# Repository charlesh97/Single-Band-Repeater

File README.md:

# Single Band Repeater
## Uplink 698-719MHz
## Downlink 728-746MHz

Archived project. [Schematic](https://gitlab.com/chood2/single-band-repeater/-/blob/main/singleBandRepeater.pdf),[PCB](https://gitlab.com/chood2/single-band-repeater/-/blob/main/Screen%20Shot%202020-11-10%20at%2012.03.37%20PM.png)

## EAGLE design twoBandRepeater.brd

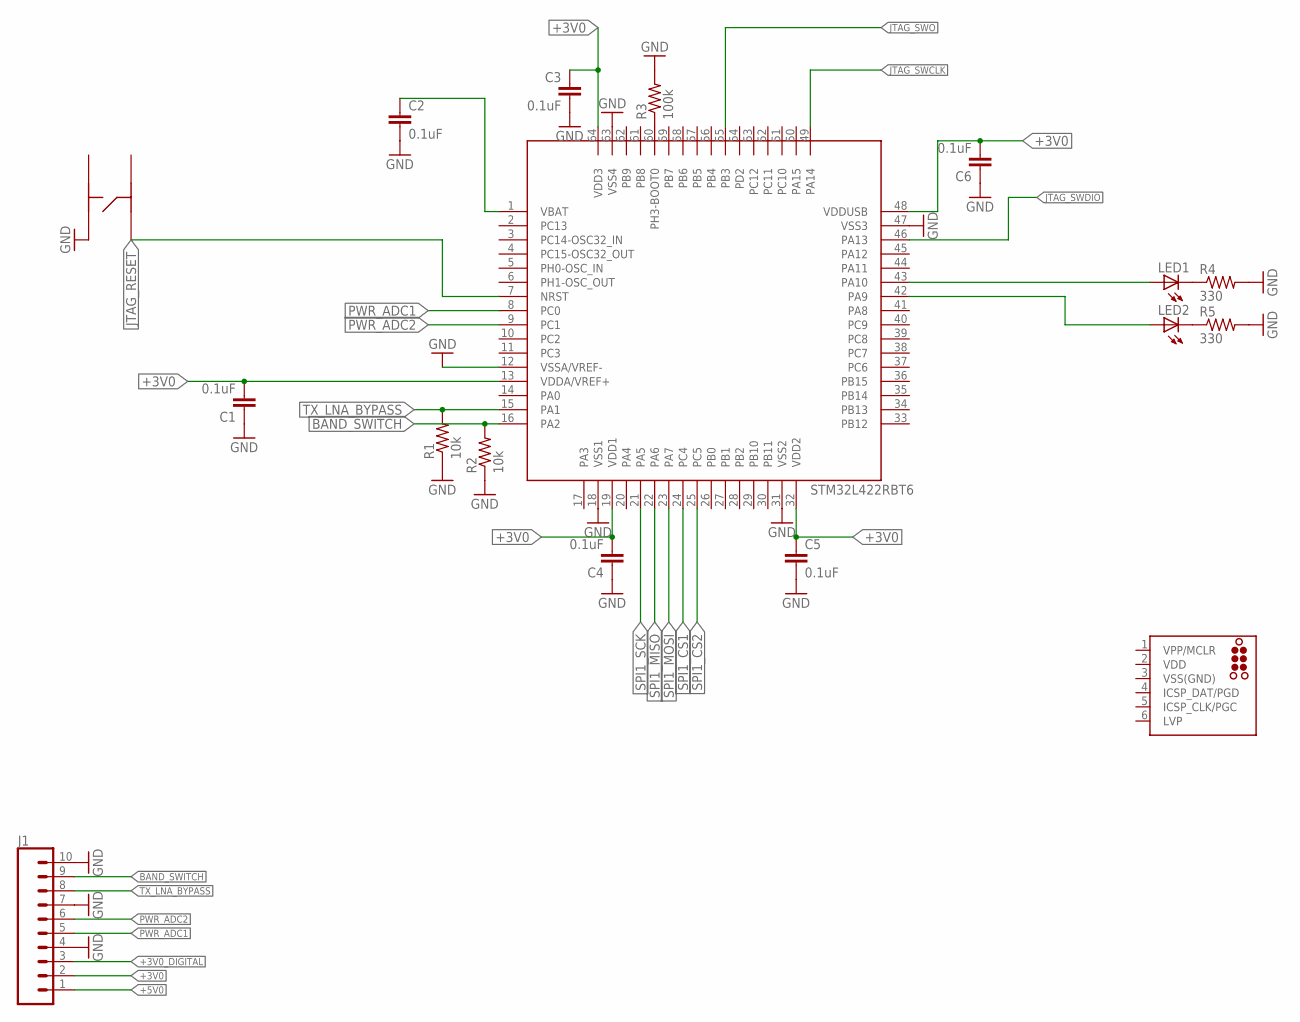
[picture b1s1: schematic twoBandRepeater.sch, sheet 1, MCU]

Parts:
C1, C2, C3, C4, C5, C6: 0.1uF; C0402
J1: CONN_10"; 1X10
J2: TC2030-MCP
LED1, LED2: LEDCHIP-LED0603; CHIP-LED0603
R1, R2: 10k; R0402
R3: 100k; R0402
R4, R5: 330; R0402
S1: KMR731NG
U1: STM32L422RBT6; QFP50P1200X1200X160-64

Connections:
+3V0: C1.2, C3.1, C4.2, C5.1, C6.2, J1.2, U1.13 (VDDA/VREF+), U1.19 (VDD1), U1.32 (VDD2), U1.48 (VDDUSB), U1.64 (VDD3); also elsewhere on the board
+3V0_DIGITAL: J1.3; also elsewhere on the board
+5V0: J1.1; also elsewhere on the board
BAND_SWITCH: J1.9, R2.2, U1.16 (PA2); also elsewhere on the board
GND: C1.1, C2.2, C3.2, C4.1, C5.2, C6.1, J1.4, J1.7, J1.10, R1.1, R2.1, R3.2, R4.2, R5.2, S1.P$3, U1.12 (VSSA/VREF-), U1.18 (VSS1), U1.31 (VSS2), U1.47 (VSS3), U1.63 (VSS4); also elsewhere on the board
JTAG_RESET: S1.P$2, U1.7 (NRST)
JTAG_SWCLK: U1.49 (PA14)
JTAG_SWDIO: U1.46 (PA13)
JTAG_SWO: U1.55 (PB3)
unnamed: C2.1, U1.1 (VBAT)
unnamed: LED1.C, R4.1
unnamed: LED2.C, R5.1
unnamed: LED2.A, U1.42 (PA9)
unnamed: LED1.A, U1.43 (PA10)
unnamed: R3.1, U1.60 (PH3-BOOT0)
PWR_ADC1: J1.5, U1.8 (PC0); also elsewhere on the board
PWR_ADC2: J1.6, U1.9 (PC1); also elsewhere on the board
SPI1_CS1: U1.24 (PC4); also elsewhere on the board
SPI1_CS2: U1.25 (PC5); also elsewhere on the board
SPI1_MISO: U1.22 (PA6); also elsewhere on the board
SPI1_MOSI: U1.23 (PA7); also elsewhere on the board
SPI1_SCK: U1.21 (PA5); also elsewhere on the board
TX_LNA_BYPASS: J1.8, R1.2, U1.15 (PA1); also elsewhere on the board
VDD: J2.2 (VDD)
VSS(GND): J2.3 (VSS(GND))

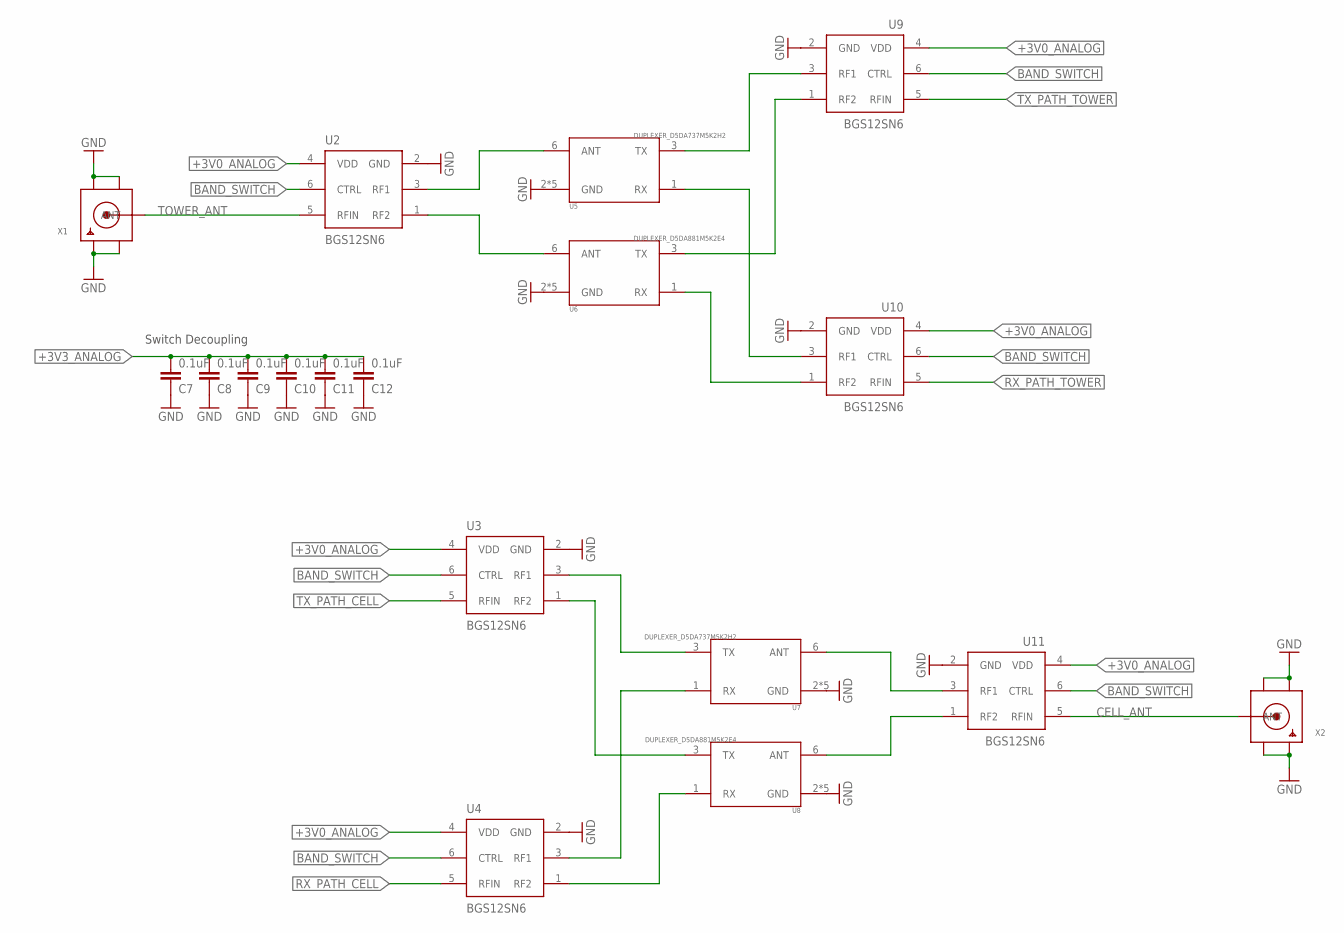
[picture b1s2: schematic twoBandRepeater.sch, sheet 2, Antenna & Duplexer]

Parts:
C7, C8, C9, C10, C11, C12: 0.1uF; C0402
U2, U3, U4, U9, U10, U11: BGS12SN6; INF-PG-TSNP-6-2
U5, U7: DUPLEXER_D5DA737M5K2H2; TAIYO_YUDEN_DUPLEX_1.8X1.4
U6, U8: DUPLEXER_D5DA881M5K2E4; TAIYO_YUDEN_DUPLEX_1.8X1.4
X1, X2: SMACONNECTORSMA_DIP; SMA_DIP

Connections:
+3V0_ANALOG: U2.4 (VDD), U3.4 (VDD), U4.4 (VDD), U9.4 (VDD), U10.4 (VDD), U11.4 (VDD); also elsewhere on the board
+3V3_ANALOG: C7.2, C8.2, C9.2, C10.2, C11.2, C12.2
BAND_SWITCH: U2.6 (CTRL), U3.6 (CTRL), U4.6 (CTRL), U9.6 (CTRL), U10.6 (CTRL), U11.6 (CTRL); also elsewhere on the board
CELL_ANT: U11.5 (RFIN), X2.ANTENNA (ANT)
GND: C7.1, C8.1, C9.1, C10.1, C11.1, C12.1, U2.2 (GND), U3.2 (GND), U4.2 (GND), U5.2 (GND), U5.4 (GND), U5.5 (GND), U5.7 (GND), U5.8 (GND), U6.2 (GND), U6.4 (GND), U6.5 (GND), U6.7 (GND), U6.8 (GND), U7.2 (GND), U7.4 (GND), U7.5 (GND), U7.7 (GND), U7.8 (GND), U8.2 (GND), U8.4 (GND), U8.5 (GND), U8.7 (GND), U8.8 (GND), U9.2 (GND), U10.2 (GND), U11.2 (GND), X1.GND1, X1.GND2, X1.GND3, X1.GND4, X2.GND1, X2.GND2, X2.GND3, X2.GND4; also elsewhere on the board
unnamed: U2.3 (RF1), U5.6 (ANT)
unnamed: U2.1 (RF2), U6.6 (ANT)
unnamed: U5.3 (TX), U9.3 (RF1)
unnamed: U6.3 (TX), U9.1 (RF2)
unnamed: U5.1 (RX), U10.3 (RF1)
unnamed: U6.1 (RX), U10.1 (RF2)
unnamed: U7.6 (ANT), U11.3 (RF1)
unnamed: U8.6 (ANT), U11.1 (RF2)
unnamed: U3.3 (RF1), U7.3 (TX)
unnamed: U3.1 (RF2), U8.3 (TX)
unnamed: U4.3 (RF1), U7.1 (RX)
unnamed: U4.1 (RF2), U8.1 (RX)
RX_PATH_CELL: U4.5 (RFIN); also elsewhere on the board
RX_PATH_TOWER: U10.5 (RFIN); also elsewhere on the board
TOWER_ANT: U2.5 (RFIN), X1.ANTENNA (ANT)
TX_PATH_CELL: U3.5 (RFIN); also elsewhere on the board
TX_PATH_TOWER: U9.5 (RFIN); also elsewhere on the board

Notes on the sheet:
Switch Decoupling

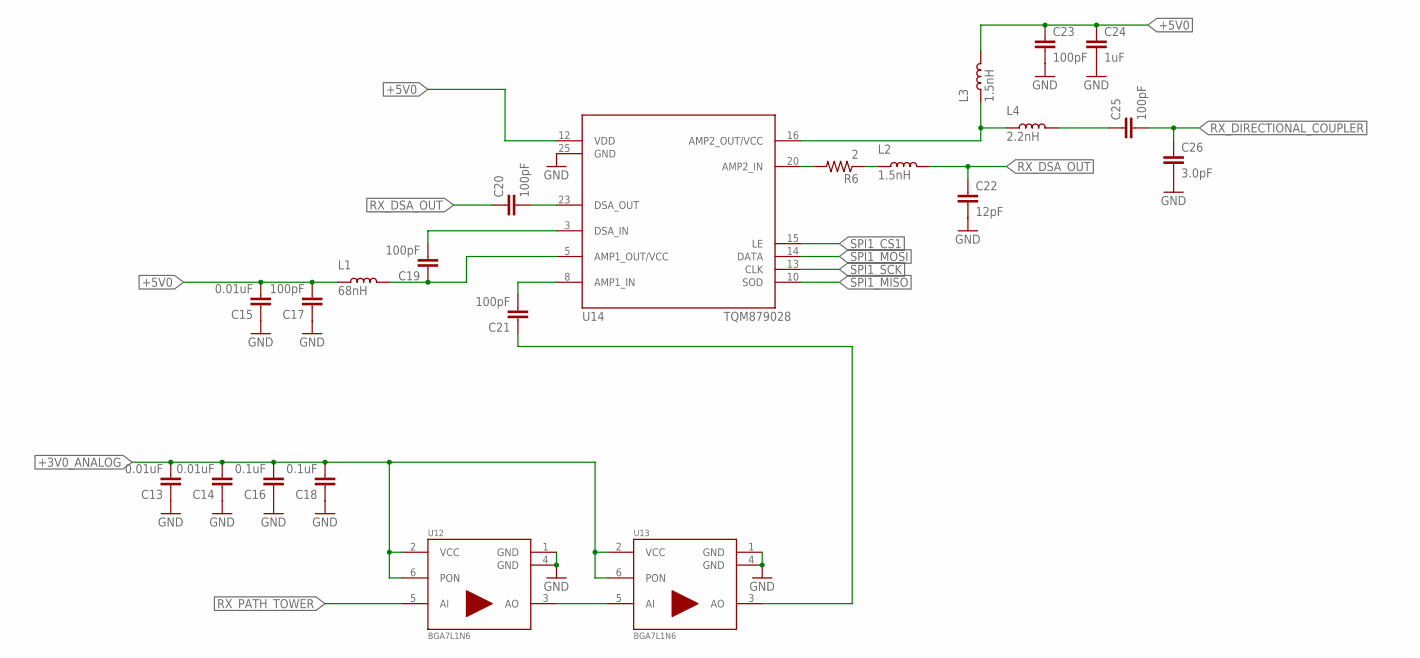
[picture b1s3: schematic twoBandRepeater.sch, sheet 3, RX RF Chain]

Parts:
C13, C14, C15: 0.01uF; C0402
C16, C18: 0.1uF; C0402
C17, C19, C20, C21, C23, C25: 100pF; C0402
C22: 12pF; C0402
C24: 1uF; C0402
C26: 3.0pF; C0402
L1: 68nH; 0402
L2, L3: 1.5nH; 0402
L4: 2.2nH; 0402
R6: 2; R0402
U12, U13: BGA7L1N6; INF-PG-TSNP-6-2
U14: TQM879028; QFN50P400X400X100-25T270N

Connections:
+3V0_ANALOG: C13.2, C14.2, C16.2, C18.2, U12.2 (VCC), U12.6 (PON), U13.2 (VCC), U13.6 (PON); also elsewhere on the board
+5V0: C15.2, C17.2, C23.1, C24.1, L1.1, L3.2, U14.12 (VDD); also elsewhere on the board
GND: C13.1, C14.1, C15.1, C16.1, C17.1, C18.1, C22.2, C23.2, C24.2, C26.2, U12.1 (GND), U12.4 (GND), U13.1 (GND), U13.4 (GND), U14.25 (GND); also elsewhere on the board
unnamed: U12.3 (AO), U13.5 (AI)
unnamed: C21.1, U13.3 (AO)
unnamed: C21.2, U14.8 (AMP1_IN)
unnamed: C19.1, L1.2, U14.5 (AMP1_OUT/VCC)
unnamed: C20.2, U14.23 (DSA_OUT)
unnamed: C19.2, U14.3 (DSA_IN)
unnamed: L3.1, L4.1, U14.16 (AMP2_OUT/VCC)
unnamed: L2.1, R6.1
unnamed: R6.2, U14.20 (AMP2_IN)
unnamed: C25.1, L4.2
RX_DIRECTIONAL_COUPLER: C25.2, C26.1; also elsewhere on the board
RX_DSA_OUT: C20.1, C22.1, L2.2
RX_PATH_TOWER: U12.5 (AI); also elsewhere on the board
SPI1_CS1: U14.15 (LE); also elsewhere on the board
SPI1_MISO: U14.10 (SOD); also elsewhere on the board
SPI1_MOSI: U14.14 (DATA); also elsewhere on the board
SPI1_SCK: U14.13 (CLK); also elsewhere on the board

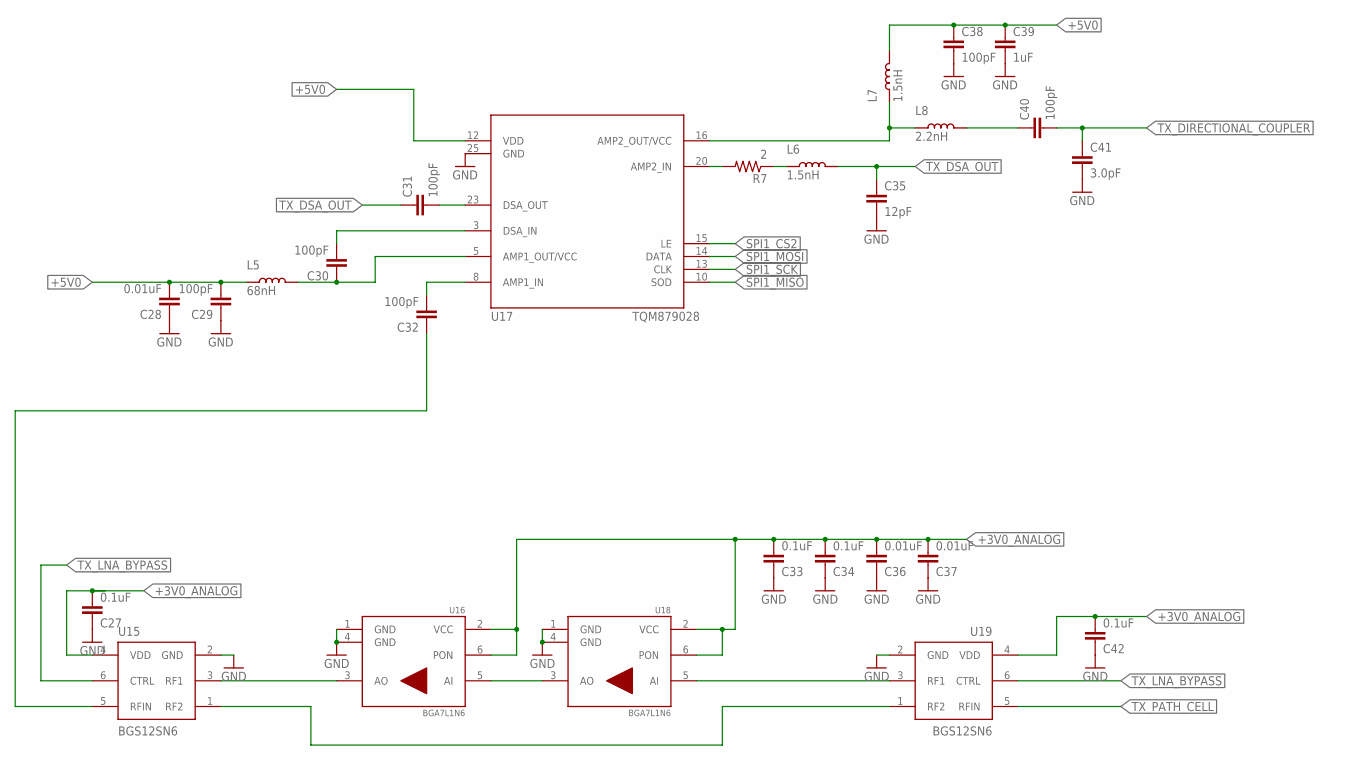
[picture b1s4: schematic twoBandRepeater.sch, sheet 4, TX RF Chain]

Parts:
C27, C33, C34, C42: 0.1uF; C0402
C28, C36, C37: 0.01uF; C0402
C29, C30, C31, C32, C38, C40: 100pF; C0402
C35: 12pF; C0402
C39: 1uF; C0402
C41: 3.0pF; C0402
L5: 68nH; 0402
L6, L7: 1.5nH; 0402
L8: 2.2nH; 0402
R7: 2; R0402
U15, U19: BGS12SN6; INF-PG-TSNP-6-2
U16, U18: BGA7L1N6; INF-PG-TSNP-6-2
U17: TQM879028; QFN50P400X400X100-25T270N

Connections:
+3V0_ANALOG: C27.2, C33.2, C34.2, C36.2, C37.2, C42.2, U15.4 (VDD), U16.2 (VCC), U16.6 (PON), U18.2 (VCC), U18.6 (PON), U19.4 (VDD); also elsewhere on the board
+5V0: C28.2, C29.2, C38.1, C39.1, L5.1, L7.2, U17.12 (VDD); also elsewhere on the board
GND: C27.1, C28.1, C29.1, C33.1, C34.1, C35.2, C36.1, C37.1, C38.2, C39.2, C41.2, C42.1, U15.2 (GND), U16.1 (GND), U16.4 (GND), U17.25 (GND), U18.1 (GND), U18.4 (GND), U19.2 (GND); also elsewhere on the board
unnamed: U16.5 (AI), U18.3 (AO)
unnamed: C32.2, U17.8 (AMP1_IN)
unnamed: C30.1, L5.2, U17.5 (AMP1_OUT/VCC)
unnamed: C30.2, U17.3 (DSA_IN)
unnamed: C31.2, U17.23 (DSA_OUT)
unnamed: L6.1, R7.1
unnamed: R7.2, U17.20 (AMP2_IN)
unnamed: L7.1, L8.1, U17.16 (AMP2_OUT/VCC)
unnamed: C40.1, L8.2
unnamed: U15.3 (RF1), U16.3 (AO)
unnamed: U18.5 (AI), U19.3 (RF1)
unnamed: U15.1 (RF2), U19.1 (RF2)
unnamed: C32.1, U15.5 (RFIN)
SPI1_CS2: U17.15 (LE); also elsewhere on the board
SPI1_MISO: U17.10 (SOD); also elsewhere on the board
SPI1_MOSI: U17.14 (DATA); also elsewhere on the board
SPI1_SCK: U17.13 (CLK); also elsewhere on the board
TX_DIRECTIONAL_COUPLER: C40.2, C41.1; also elsewhere on the board
TX_DSA_OUT: C31.1, C35.1, L6.2
TX_LNA_BYPASS: U15.6 (CTRL), U19.6 (CTRL); also elsewhere on the board
TX_PATH_CELL: U19.5 (RFIN); also elsewhere on the board

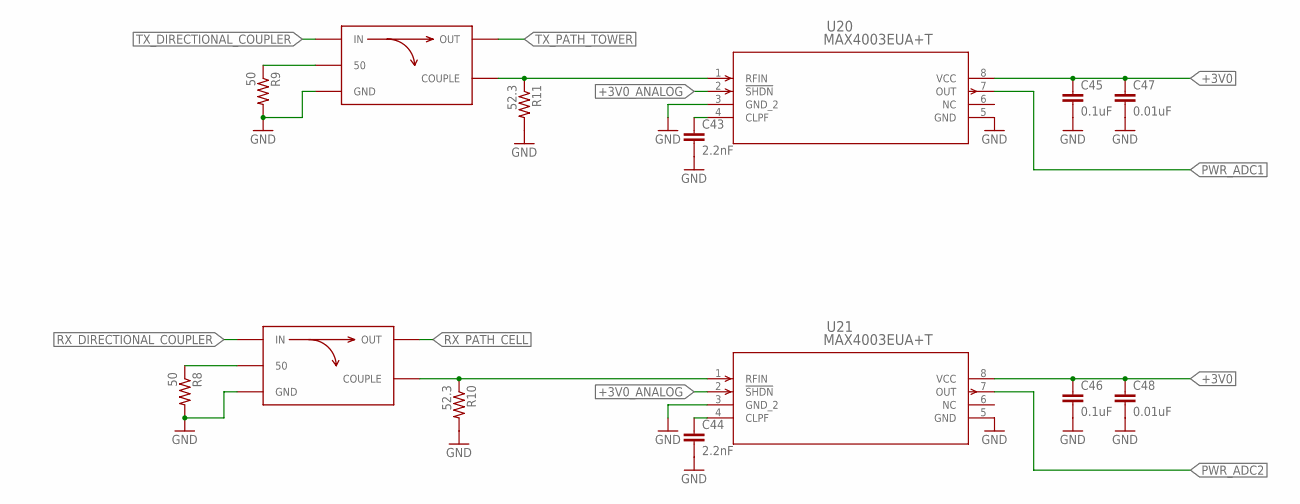
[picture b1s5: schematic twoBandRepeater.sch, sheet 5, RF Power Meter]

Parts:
C43, C44: 2.2nF; C0402
C45, C46: 0.1uF; C0402
C47, C48: 0.01uF; C0402
HY1, HY2: HHM22152A2
R8, R9: 50; R0402
R10, R11: 52.3; R0402
U20, U21: MAX4003EUA+T; 21-0036K

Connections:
+3V0: C45.1, C46.1, C47.1, C48.1, U20.8 (VCC), U21.8 (VCC); also elsewhere on the board
+3V0_ANALOG: U20.2 (!SHDN), U21.2 (!SHDN); also elsewhere on the board
GND: C43.2, C44.2, C45.2, C46.2, C47.2, C48.2, HY1.P$2 (GND), HY1.P$5 (GND), HY2.P$2 (GND), HY2.P$5 (GND), R8.2, R9.2, R10.2, R11.2, U20.3 (GND_2), U20.5 (GND), U21.3 (GND_2), U21.5 (GND); also elsewhere on the board
unnamed: HY2.P$4 (50), R9.1
unnamed: C43.1, U20.4 (CLPF)
unnamed: HY2.P$6 (COUPLE), R11.1, U20.1 (RFIN)
unnamed: HY1.P$4 (50), R8.1
unnamed: C44.1, U21.4 (CLPF)
unnamed: HY1.P$6 (COUPLE), R10.1, U21.1 (RFIN)
PWR_ADC1: U20.7 (OUT); also elsewhere on the board
PWR_ADC2: U21.7 (OUT); also elsewhere on the board
RX_DIRECTIONAL_COUPLER: HY1.P$1 (IN); also elsewhere on the board
RX_PATH_CELL: HY1.P$3 (OUT); also elsewhere on the board
TX_DIRECTIONAL_COUPLER: HY2.P$1 (IN); also elsewhere on the board
TX_PATH_TOWER: HY2.P$3 (OUT); also elsewhere on the board

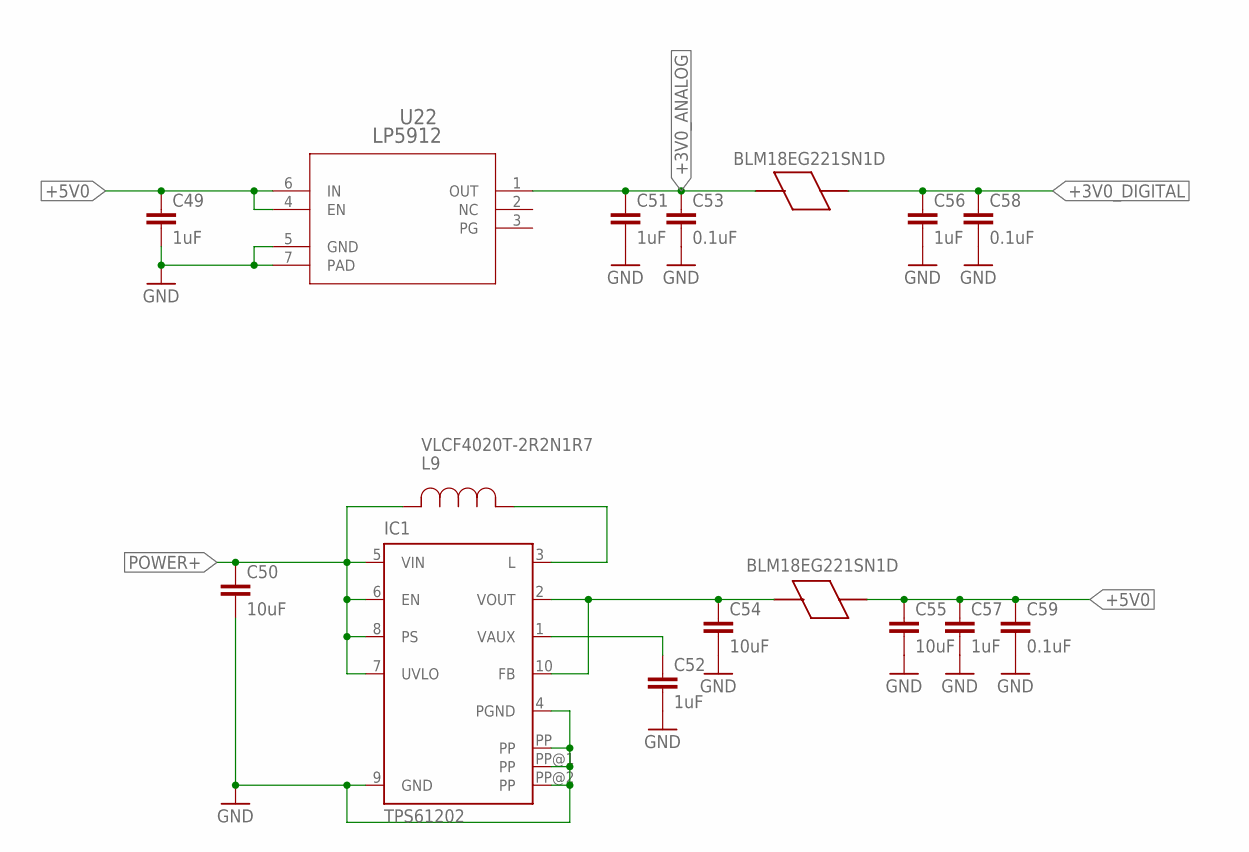
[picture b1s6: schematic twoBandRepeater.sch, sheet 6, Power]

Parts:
C49, C51, C52, C56, C57: 1uF; C0402
C50, C54, C55: 10uF; C0805
C53, C58, C59: 0.1uF; C0402
IC1: TPS61202; S-PDSO-N10
L9: VLCF4020T-2R2N1R7; IND_4028
L10, L11: BLM18EG221SN1D; IND_BLM18_0603
U22: LP5912; DRV0006A

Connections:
+3V0_ANALOG: C51.1, C53.1, L10.1, U22.1 (OUT); also elsewhere on the board
+3V0_DIGITAL: C56.1, C58.1, L10.2; also elsewhere on the board
+5V0: C49.1, C55.1, C57.1, C59.1, L11.2, U22.4 (EN), U22.6 (IN); also elsewhere on the board
GND: C49.2, C50.2, C51.2, C52.2, C53.2, C54.2, C55.2, C56.2, C57.2, C58.2, C59.2, IC1.4 (PGND), IC1.9 (GND), IC1.PP, IC1.PP@1 (PP), IC1.PP@2 (PP), U22.5 (GND), U22.7 (PAD); also elsewhere on the board
unnamed: IC1.3 (L), L9.1
unnamed: C54.1, IC1.2 (VOUT), IC1.10 (FB), L11.1
unnamed: C52.1, IC1.1 (VAUX)
POWER+: C50.1, IC1.5 (VIN), IC1.6 (EN), IC1.7 (UVLO), IC1.8 (PS), L9.2

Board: 2 copper layers, 113 parts (0 on the bottom side), 77 nets, no tracks yet.

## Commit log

2022-02-06 Configure SAST in `.gitlab-ci.yml`, creating this file if it does not already exist
2022-02-06 Adding files from Google Drive

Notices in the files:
parts and their libraries:
SparkFun-Connectors: Licensing: Creative Commons ShareAlike 4.0 International - https://creativecommons.org/licenses/by-sa/4.0
Tag-Connect-Footprints: ©2009 ROFA.cz - modified and updated by Robert Darlington ‹rdarlington@gmail.com›
